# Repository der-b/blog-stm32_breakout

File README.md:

# STM32 Breakout

This Project contains all files for my first self designed breakout board with an STM32F070CBT6 microcontroller.

The *schematic* subfolder contains all files related to the board design
The *software* subfolder contains two example firmwares.
In *img* you can find images of the assembled  board.

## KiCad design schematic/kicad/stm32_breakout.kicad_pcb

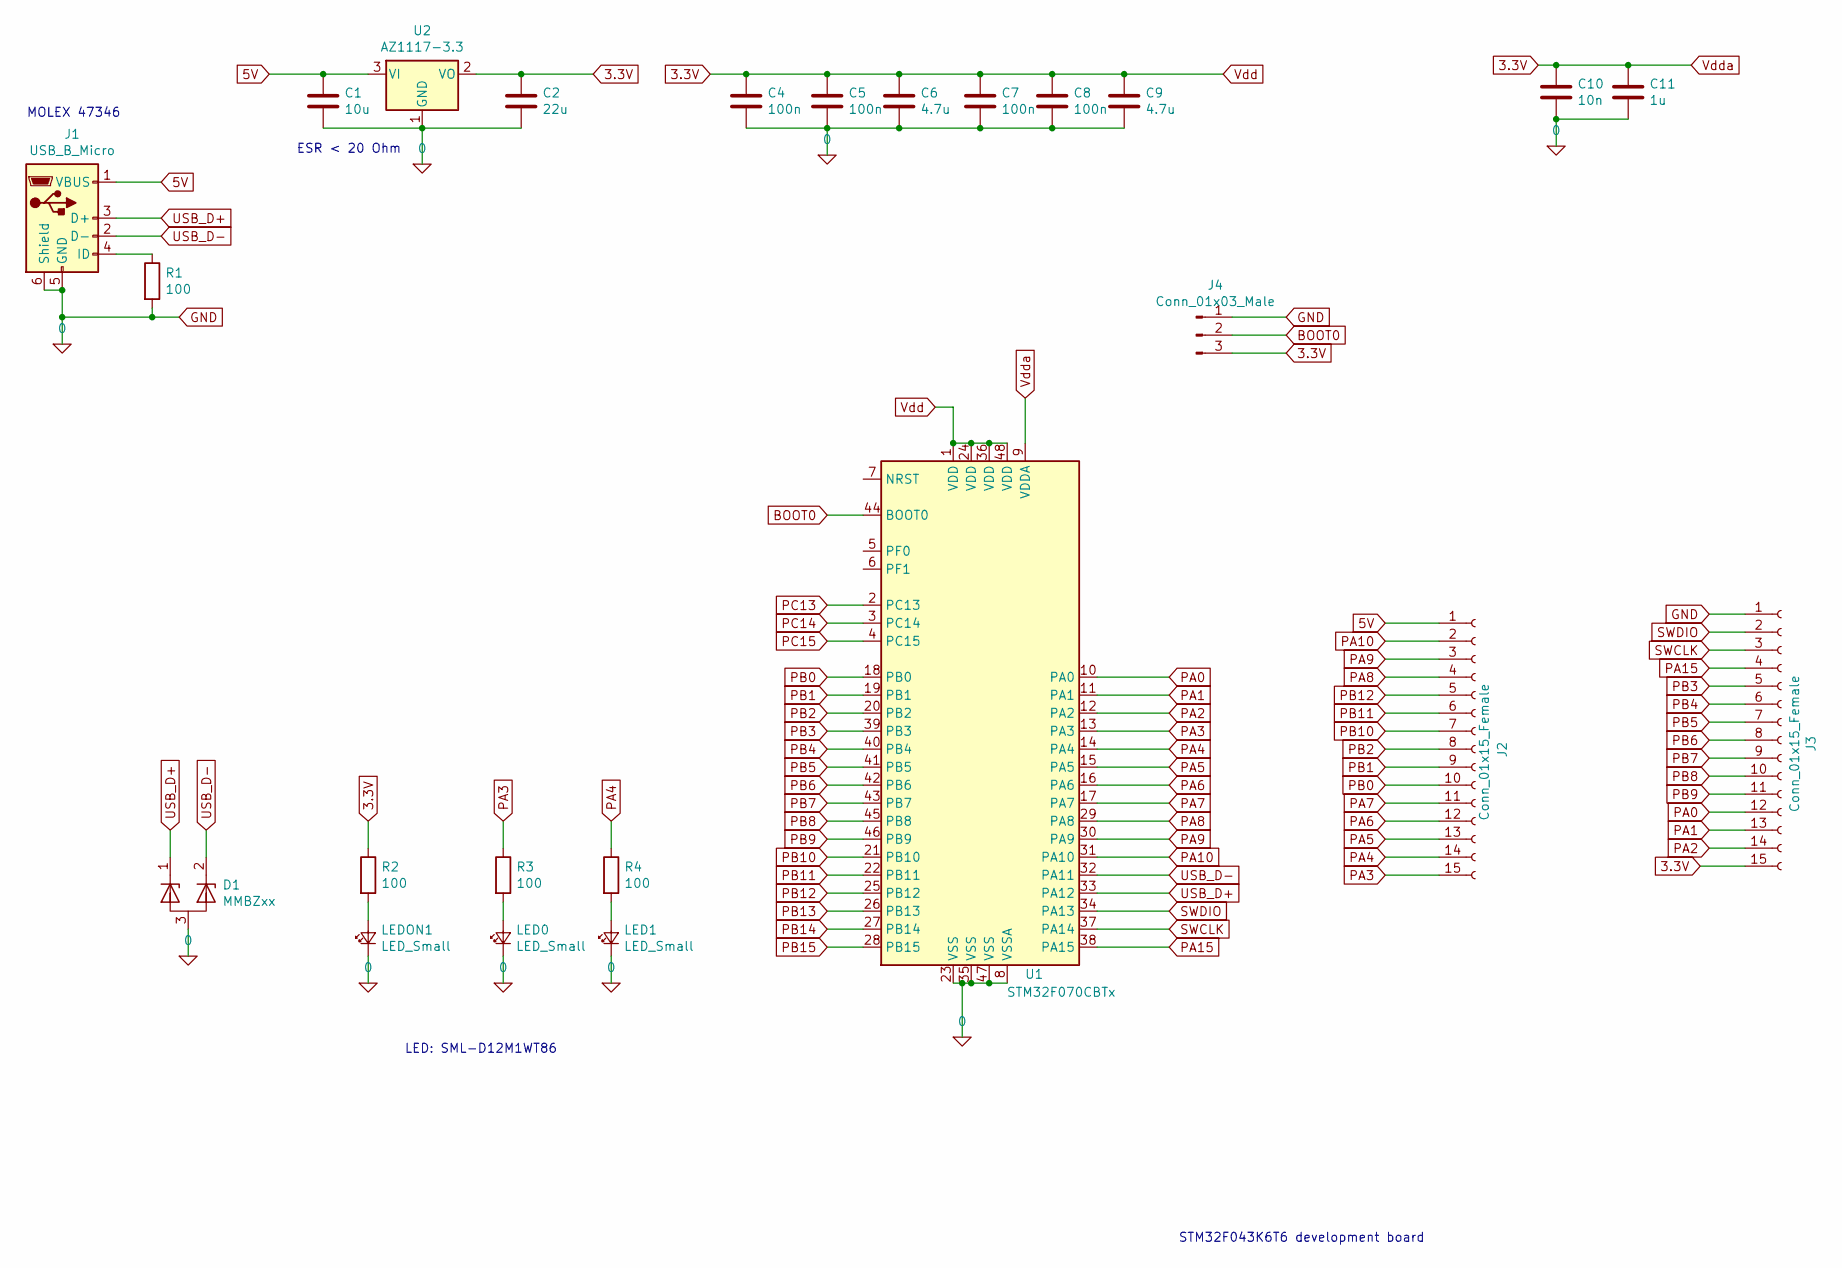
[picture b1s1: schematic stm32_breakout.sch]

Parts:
C1: 10u; LED_0603_1608Metric
C2: 22u; LED_0603_1608Metric
C4, C5, C7, C8: 100n; LED_0603_1608Metric
C6, C9: 4.7u; LED_0603_1608Metric
C10: 10n; LED_0603_1608Metric
C11: 1u; LED_0603_1608Metric
D1: MMBZxx; SOT-23
J1: USB_B_Micro; USB_Micro-B_Molex_47346-0001
J2, J3: Conn_01x15_Female; PinHeader_1x15_P2.54mm_Vertical
J4: Conn_01x03_Male; PinHeader_1x03_P2.54mm_Vertical
LED0, LED1: LED_Small; LED_0603_1608Metric
LEDON1: LED_Small; LED_0603_1608Metric
R1, R2, R3, R4: 100; LED_0603_1608Metric
U1: STM32F070CBTx; LQFP-48_7x7mm_P0.5mm
U2: AZ1117-3.3; SOT-223

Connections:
3.3V: C2.1, C4.1, C5.1, C6.1, C7.1, C8.1, C9.1, C10.1, C11.1, J3.15, J4.3, R2.1, U1.1 (VDD), U1.9 (VDDA), U1.24 (VDD), U1.36 (VDD), U1.48 (VDD), U2.2 (VO)
5V: C1.1, J1.1 (VBUS), J2.1, U2.3 (VI)
BOOT0: J4.2, U1.44 (BOOT0)
GND: C1.2, C2.2, C4.2, C5.2, C6.2, C7.2, C8.2, C9.2, C10.2, C11.2, D1.3 (A), J1.5 (GND), J1.6 (Shield), J3.1, J4.1, LED0.1 (K), LED1.1 (K), LEDON1.1 (K), R1.2, U1.8 (VSSA), U1.23 (VSS), U1.35 (VSS), U1.47 (VSS), U2.1 (GND); also elsewhere on the board
unnamed: J1.4 (ID), R1.1
unnamed: LED0.2 (A), R3.2
unnamed: LED1.2 (A), R4.2
unnamed 7: LEDON1.2 (A), R2.2; also elsewhere on the board
PA0: J3.12, U1.10 (PA0)
PA1: J3.13, U1.11 (PA1)
PA2: J3.14, U1.12 (PA2)
PA3: J2.15, R3.1, U1.13 (PA3)
PA4: J2.14, R4.1, U1.14 (PA4)
PA5: J2.13, U1.15 (PA5)
PA6: J2.12, U1.16 (PA6)
PA7: J2.11, U1.17 (PA7)
PA8: J2.4, U1.29 (PA8)
PA9: J2.3, U1.30 (PA9)
PA10: J2.2, U1.31 (PA10)
PA15: J3.4, U1.38 (PA15)
PB0: J2.10, U1.18 (PB0)
PB1: J2.9, U1.19 (PB1)
PB2: J2.8, U1.20 (PB2)
PB3: J3.5, U1.39 (PB3)
PB4: J3.6, U1.40 (PB4)
PB5: J3.7, U1.41 (PB5)
PB6: J3.8, U1.42 (PB6)
PB7: J3.9, U1.43 (PB7)
PB8: J3.10, U1.45 (PB8)
PB9: J3.11, U1.46 (PB9)
PB10: J2.7, U1.21 (PB10)
PB11: J2.6, U1.22 (PB11)
PB12: J2.5, U1.25 (PB12)
PB13: U1.26 (PB13)
PB14: U1.27 (PB14)
PB15: U1.28 (PB15)
PC13: U1.2 (PC13)
PC14: U1.3 (PC14)
PC15: U1.4 (PC15)
SWCLK: J3.3, U1.37 (PA14)
SWDIO: J3.2, U1.34 (PA13)
USB_D+: D1.1 (K), J1.3 (D+), U1.33 (PA12)
USB_D-: D1.2 (K), J1.2 (D-), U1.32 (PA11)

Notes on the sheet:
ESR < 20 Ohm
LED: SML-D12M1WT86
MOLEX 47346
STM32F043K6T6 development board

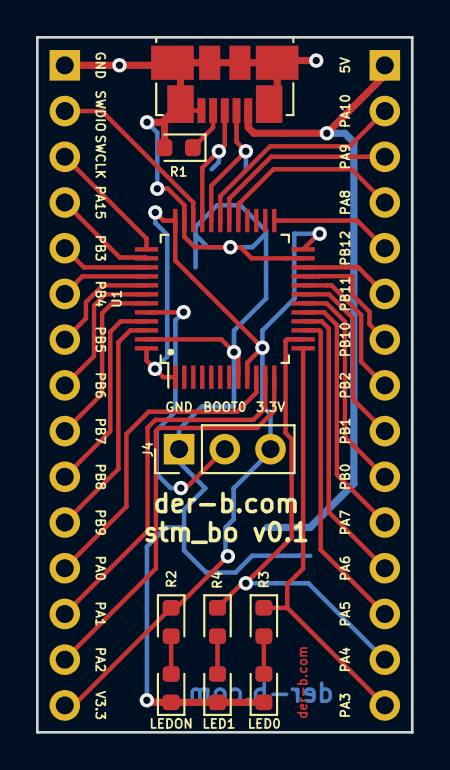
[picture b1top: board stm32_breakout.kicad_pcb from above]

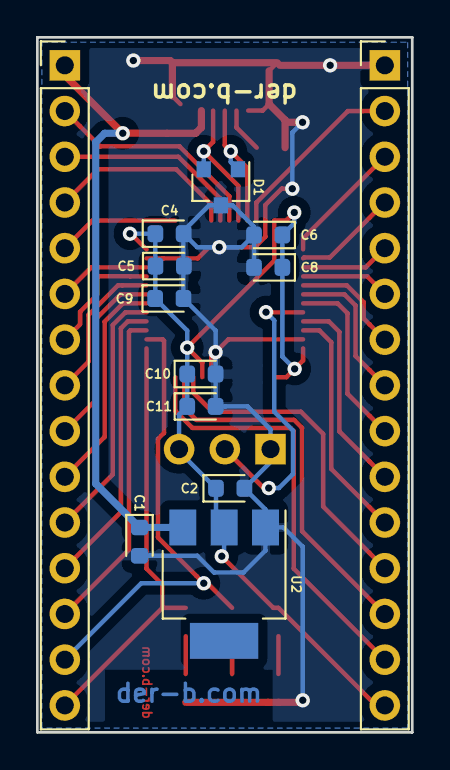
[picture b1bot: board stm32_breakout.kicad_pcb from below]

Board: 2 copper layers, 20.8 x 38.6 mm, 23 parts (13 on the bottom side), 37 nets.

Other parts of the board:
LEDON: LED_Small; LED_0603_1608Metric

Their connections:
GND: LEDON.1; also elsewhere on the board
unnamed 7: LEDON.2; also elsewhere on the board

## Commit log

2020-02-29 Added all files.
2020-02-29 Fix(): Format erer in READMEs.
2020-02-29 Fix(): comments.
2020-03-01 Changed the USB Product ID to the test ID of the pid.codes project: http://pid.codes/1209/0001/
2020-03-01 Add Open Hardwar License TAPR
